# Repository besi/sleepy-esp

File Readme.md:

# Sleepynotes for ESP

Take sleepy notes without looking at a screen.

## Architecture

At the time of writing there does not seem to be a way of implementing a HID host via Bluetooth so the project is split up into two parts:

### A) Bluetooth HID

This part is written in the native Espressif IDF environment using IDF Version 6.1.
First a connection to a bluetooth keyboard is established. If the keyboard is named "Sleepynotes" the connection should be established automatically.

Once the pairing is done the HID messages received from the keyboard are read and sent via UART in the following format (spelling out 'Hello'):

```
HID-00-00-00-00-00-00-00-00
HID-02-00-00-00-00-00-00-00
HID-02-00-0b-00-00-00-00-00
HID-02-00-00-00-00-00-00-00
HID-00-00-00-00-00-00-00-00
HID-00-00-08-00-00-00-00-00
HID-00-00-00-00-00-00-00-00
HID-00-00-0f-00-00-00-00-00
HID-00-00-00-00-00-00-00-00
HID-00-00-0f-00-00-00-00-00
HID-00-00-00-00-00-00-00-00
HID-00-00-12-00-00-00-00-00
```

Since the ease of development is relatively low due to long compile times and old school C programming. This part is kept as simple as possible, moving more complexity to the second part of the application.

To flash the program onto an ESP32 board the following steps are required:

```bash
cd idf/
get_idf # Activate the IDF environment
idf.py build flash monitor
```

The ESP-IDF framework needs to be installed on the system (such as ~/esp-idf).

### B) Notetaking

This part is written in Micropython and the HID messages are decoded and interpreted. Any on-board peripherals such as RGB-LEDs etc. are managed by this part of the project.

## Pinout of the Micropython ESP

| Function            | GPIO |
|:--------------------|-----:|
| Neopixel            | 14   |
| Wireless Button A   |  4   |
| Wireless Button B   |  0   |
| Wireless Button C   |  2   |
| Wireless Button D   | 16   |
| Wireless Button Any | 21   |
| I2C SDA             |  9   |
| I2C SCL             | 10   |
| SPI CS              | 12   |
| SPI MOSI            | 32   |
| SPI MISO            | 27   |
| SPI CLK             | 25   |
| LDR                 | 36   |
| Button 1            | 39   |
| Button 2            | 35   |
| Button 3            | 33   |
| Button 4            | 34   |

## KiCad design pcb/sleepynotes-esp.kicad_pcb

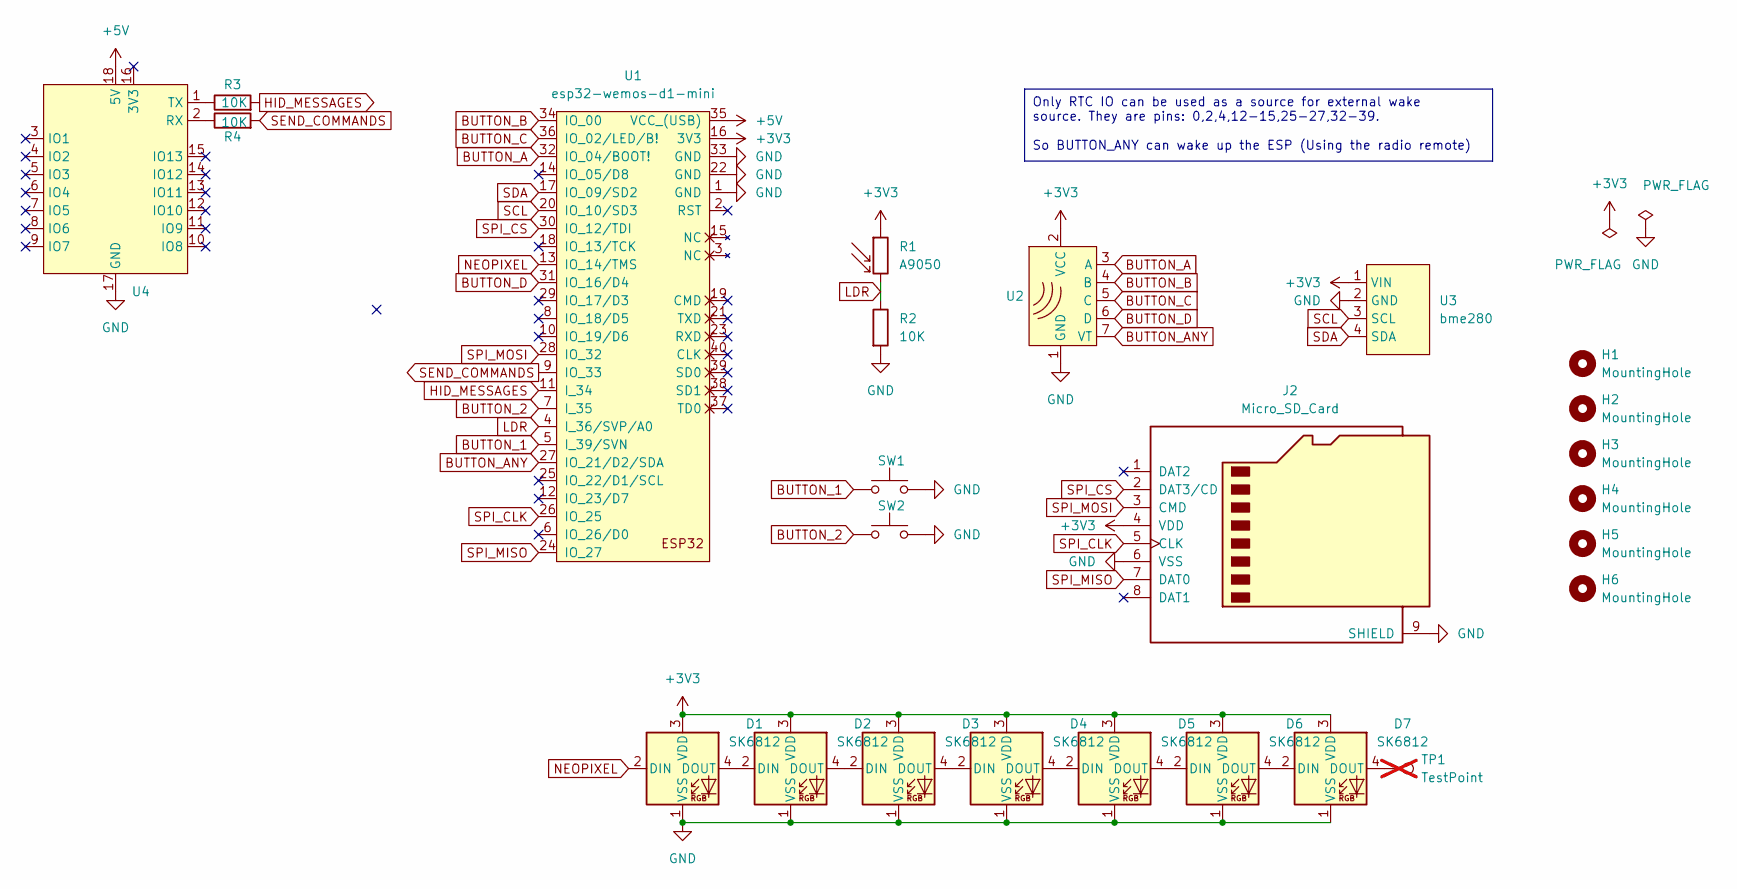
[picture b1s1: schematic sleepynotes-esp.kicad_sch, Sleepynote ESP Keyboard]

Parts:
D1, D2, D3, D4, D5, D6, D7: SK6812; LED_SK6812_PLCC4_5.0x5.0mm_P3.2mm
H1, H2, H3, H4, H5, H6: MountingHole; MountingHole_3.2mm_M3
J2: Micro_SD_Card; sd-card
R1: A9050; R_LDR_5.0x4.1mm_P3mm_Vertical
R2, R3, R4: 10K; R_Axial_DIN0207_L6.3mm_D2.5mm_P7.62mm_Horizontal
SW1, SW2: SW_Push; SW_PUSH_6mm_H7.3mm
TP1: TestPoint; PinHeader_1x01_P2.54mm_Vertical; not fitted
U1: esp32-wemos-d1-mini
U2: RX480E; rx480
U3: bme280
U4: esp32s3-supermini

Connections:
+3V3: D1.3 (VDD), D2.3 (VDD), D3.3 (VDD), D4.3 (VDD), D5.3 (VDD), D6.3 (VDD), D7.3 (VDD), J2.4 (VDD), R1.1, U1.16 (3V3), U2.2 (VCC), U3.1 (VIN)
+5V: U1.35 (VCC_(USB)), U4.18 (5V)
BUTTON_1: SW1.1, U1.5 (I_39/SVN)
BUTTON_2: SW2.1, U1.7 (I_35)
BUTTON_A: U1.32 (IO_04/BOOT!), U2.3 (A)
BUTTON_ANY: U1.27 (IO_21/D2/SDA), U2.7 (VT)
BUTTON_B: U1.34 (IO_00), U2.4 (B)
BUTTON_C: U1.36 (IO_02/LED/B!), U2.5 (C)
BUTTON_D: U1.31 (IO_16/D4), U2.6 (D)
GND: D1.1 (VSS), D2.1 (VSS), D3.1 (VSS), D4.1 (VSS), D5.1 (VSS), D6.1 (VSS), D7.1 (VSS), J2.6 (VSS), J2.9 (SHIELD), R2.2, SW1.2, SW2.2, U1.1 (GND), U1.22 (GND), U1.33 (GND), U2.1 (GND), U3.2 (GND), U4.17 (GND)
HID_MESSAGES: R3.2, U1.11 (I_34)
LDR: R1.2, R2.1, U1.4 (I_36/SVP/A0)
NEOPIXEL: D1.2 (DIN), U1.13 (IO_14/TMS)
unnamed: D1.4 (DOUT), D2.2 (DIN)
unnamed: D2.4 (DOUT), D3.2 (DIN)
unnamed: D3.4 (DOUT), D4.2 (DIN)
unnamed: D4.4 (DOUT), D5.2 (DIN)
unnamed: D5.4 (DOUT), D6.2 (DIN)
unnamed: D6.4 (DOUT), D7.2 (DIN)
unnamed: D7.4 (DOUT), TP1.1
unnamed: R4.1, U4.2 (RX)
unnamed: R3.1, U4.1 (TX)
SCL: U1.20 (IO_10/SD3), U3.3 (SCL)
SDA: U1.17 (IO_09/SD2), U3.4 (SDA)
SEND_COMMANDS: R4.2, U1.9 (IO_33)
SPI_CLK: J2.5 (CLK), U1.26 (IO_25)
SPI_CS: J2.2 (DAT3/CD), U1.30 (IO_12/TDI)
SPI_MISO: J2.7 (DAT0), U1.24 (IO_27)
SPI_MOSI: J2.3 (CMD), U1.28 (IO_32)

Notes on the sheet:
Only RTC IO can be used as a source for external wake source. They are pins: 0,2,4,12-15,25-27,32-39. So BUTTON_ANY can wake up the ESP (Using the radio remote)

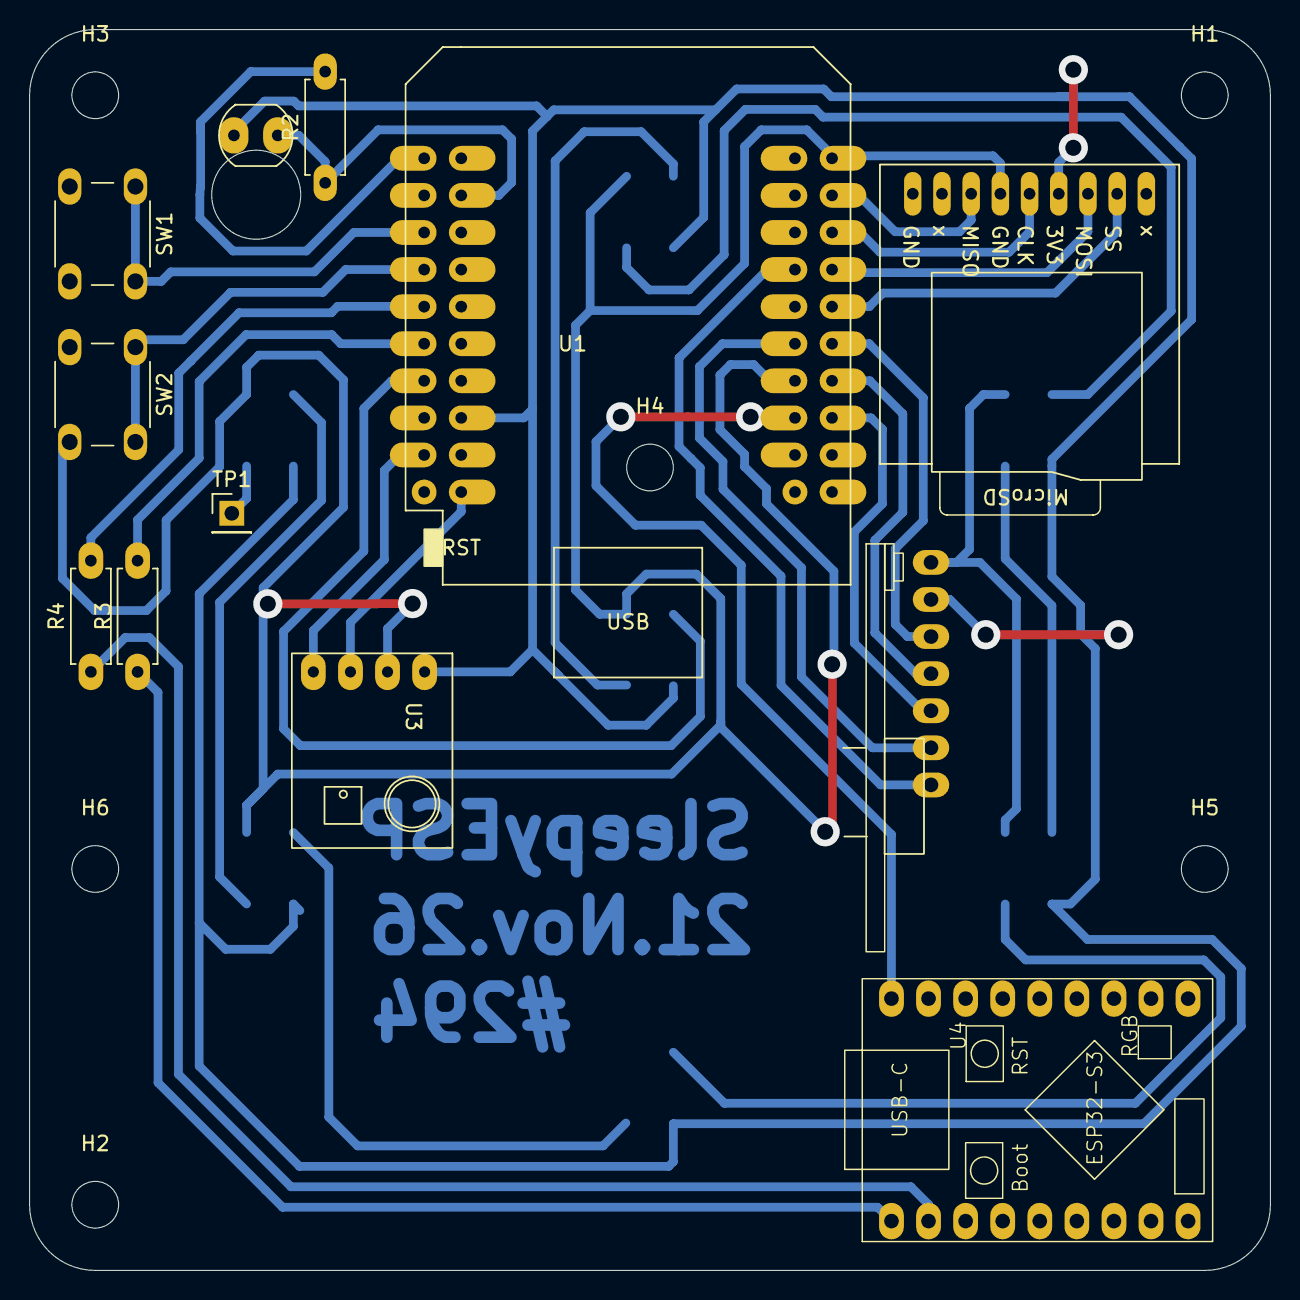
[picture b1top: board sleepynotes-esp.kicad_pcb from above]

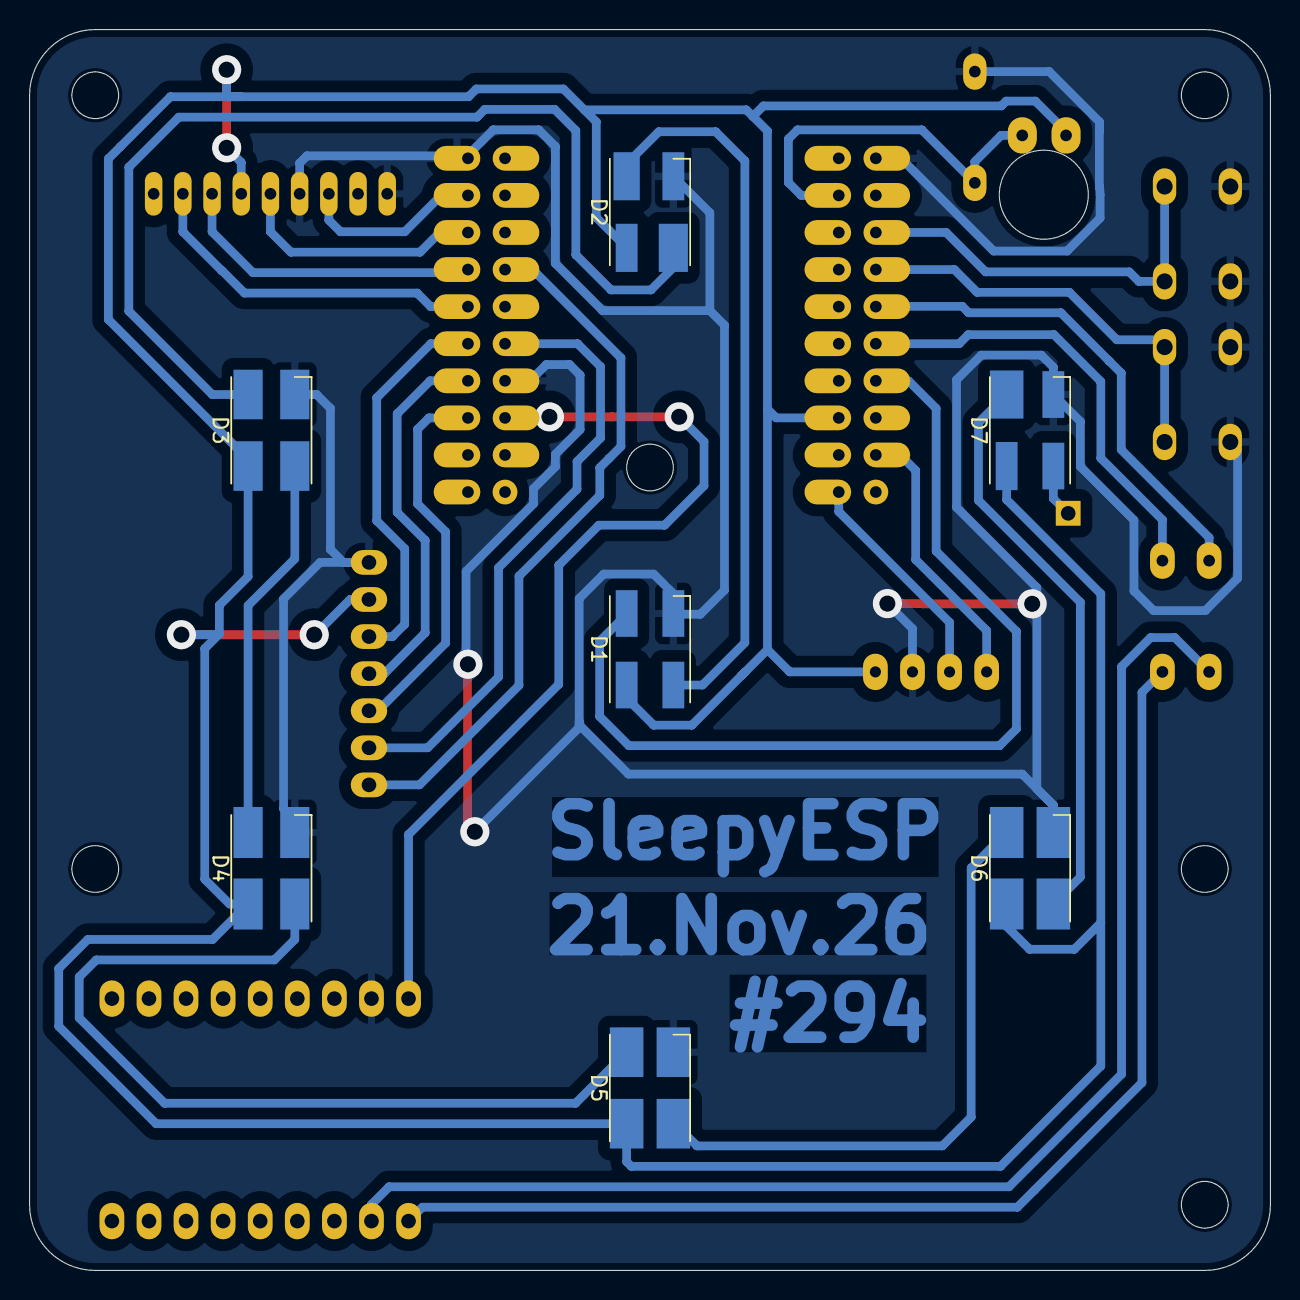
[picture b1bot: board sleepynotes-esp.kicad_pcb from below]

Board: 2 copper layers, 85.0 x 85.0 mm, 25 parts (7 on the bottom side), 29 nets.
